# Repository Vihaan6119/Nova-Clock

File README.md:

# Nova Clock

Nova Clock is a desktop alarm clock which uses a Seeed Studio XIAO ESP32-C3. It has a 2.25-inch TFT display, four mechanical keyboard switches, a piezo buzzer and all of these will be on a custom PCB with an enclosure/case where all of these will sit in. The PCB, enclosure, and firmware were all designed as part of the same project so the electronics and the case fit together as one system.

## Why I made it

I wanted to build a project that was more than just a basic clock. I wanted to learn how a real hardware product is build, from designing the PCB and enclosure to writing the firmware and planning how the final device would actually be used.
I also wanted the clock to be something I could keep improving later, especially the display styles, alarms, sounds, and the way it can be used from different device.

## Project

The final design uses a custom PCB with the XIAO ESP32-C3 as the main controller for the clock. The four switches are used for local controls like if the alarm is ringing, then the we can use the switches to turn the alarm off. The TFT display is used for the clock and other information. The buzzer make the sound for the alarms and other things which we like to add.

The enclosure was designed around the PCB so the board can be mounted securely. There is a cutout on the back of the enclosure so that we can easily connect a power/data cable. The display taped onto the lid to make it easier to keep it there without making the build more complex.

## How I planned the firmware

The firmware is included in the repository as a prototype for the hardware design. The main idea is:

- show a short Nova Clock startup animation
- play a startup beep
- display the current time
- use the buttons for local clock and alarm controls
- store alarm settings on the ESP32-C3
- connect the clock to Wi-Fi
- provide a local web interface for changing alarm and display settings
- support different display styles and alarm sound patterns (if the buzzer supports it)

The current firmware is just the PROTOTYPE and will be way different from the current version as after i get all the parts for this build, i will configure them and then properly test and see how eveything is working.

## The enclosure talk

I have started designing the case in openSAD as i thought that this will be the easiest from all the other softwares out there, and it proved me wrong. As i was making the enclosure, it was getting harder to get the precise geomatrical measurements into it, and i also could not check if the PCB all the components would fit in it. 

Then I switched to tinkercad. there i imported PCB, and made the base and the lid. But here too, i did not understand how to make the holes/cutouts in the solids/shapes. 

So then again i switched to Onshape (here i finished making it). I first imported the prototype case i build in tinker cad and tried to build on it. But failed. Then i watched a bunch of tutorials from which, i learn how onshape work. The i started making the PCB enclosure/case. Then after that was done, i imported the PCB .step file. to see if it would fit, and it didn't fit. 

Then I had assembled the full thing. i mean, got all the 3 thing and assembled it showing how it will be looking after i have all the components with me.

## Important thing about viewing the the full assemble .step file

Unfortunaltly, you have to do a little more work in order to see the full assemble 3D model. (You will also come across an error when you upload the .step file of the PCB and the full assembly file. This is due to the 3d model of the ESP32. There is nothing to worry. It is just the issue with the 3D model. I couldn't find a solution to it. )

I have used Onshape in the instruction.

* **uploading:** Import the file **Nova_Clock_Full_Assembly_V4.step** from the folder **CAD** (of my repo).
* It will take aorund 1-2 mins for it to import and load all the file into it.
* **Selecting the file form the menu:** After the import has finished, there will be load and loads of file. From there you have to open 1 file named **Nova_Clock_Full_Assembly**.

## wiring table for display soldering

| PCB Hole | Signal |
| :---: | :--- |
| **1** | GND |
| **2** | +3.3V |
| **3** | SCL |
| **4** | SDA |
| **5** | RST |
| **6** | DC |
| **7** | CS |
| **8** | BL |

The 8 display wires are soldered directly to the display and to the PCB’s J1 holes 
  
## Project images

### Case fit

### PCB

### Schematic / wiring

### Project assembly

.png>)

## Files

The repository has the KiCad project and PCB source files, the CAD source and STEP assembly, the firmware, manufacturing files, and the project images.

- `PCB/` - KiCad project, schematic, PCB layout, and manufacturing files
- `CAD/` - enclosure source files and final STEP assembly
- `Firmware/` - Nova Clock firmware
- `Production/` - production/export files
- `assets/` - screenshots and project images

## Bill of Materials

| Component | Quantity Used | Quantity in Kit | Description | Link |
|---|---:|---:|---|---|
| Seeed Studio XIAO ESP32-C3 | 1 | 1 | Main microcontroller | BLARE Kit |
| MX-style keyboard switch | 4 | 12 | Mechanical switches | BLARE Kit |
| White blank DSA keycap | 4 | 12 | Keycaps for the switches | BLARE Kit |
| 1N4148 through-hole diode | 0 | 12 | Switch matrix diodes | BLARE Kit|
| 2.25-inch TFT display | 1 | 1 | Main clock display | BLARE Kit |
| 3.3 V piezo buzzer | 1 | 1 | Startup and alarm sound | BLARE Kit |
| 2.54 mm 8-pin male header | 1 | 1 | Display connector (only for testing, the final version will have soldered ends) | BLARE Kit |
| 20 cm female-female jumper wire | 8 | 8 | Display wiring (only for testing, the final version will have soldered ends) | BLARE Kit |
| M3x5x4 heat-set insert | 6-8 | 8 | Case, PCB, and display mounting | BLARE Kit |
| M3x8 screw | 2 | 4 | PCB | BLARE Kit |
| M3x16 screw | 4 | 4 | Main enclosure screws | BLARE Kit |
| Custom 2-layer PCB | 1 | 1 | PCB designed in KiCad | [Project PCB](PCB/)  from JLCPCB. Price: $11.1-13.1|
| 3D-printed enclosure | 1 | 1 | Custom Nova Clock case | [Project CAD](CAD/) from printing Legion|

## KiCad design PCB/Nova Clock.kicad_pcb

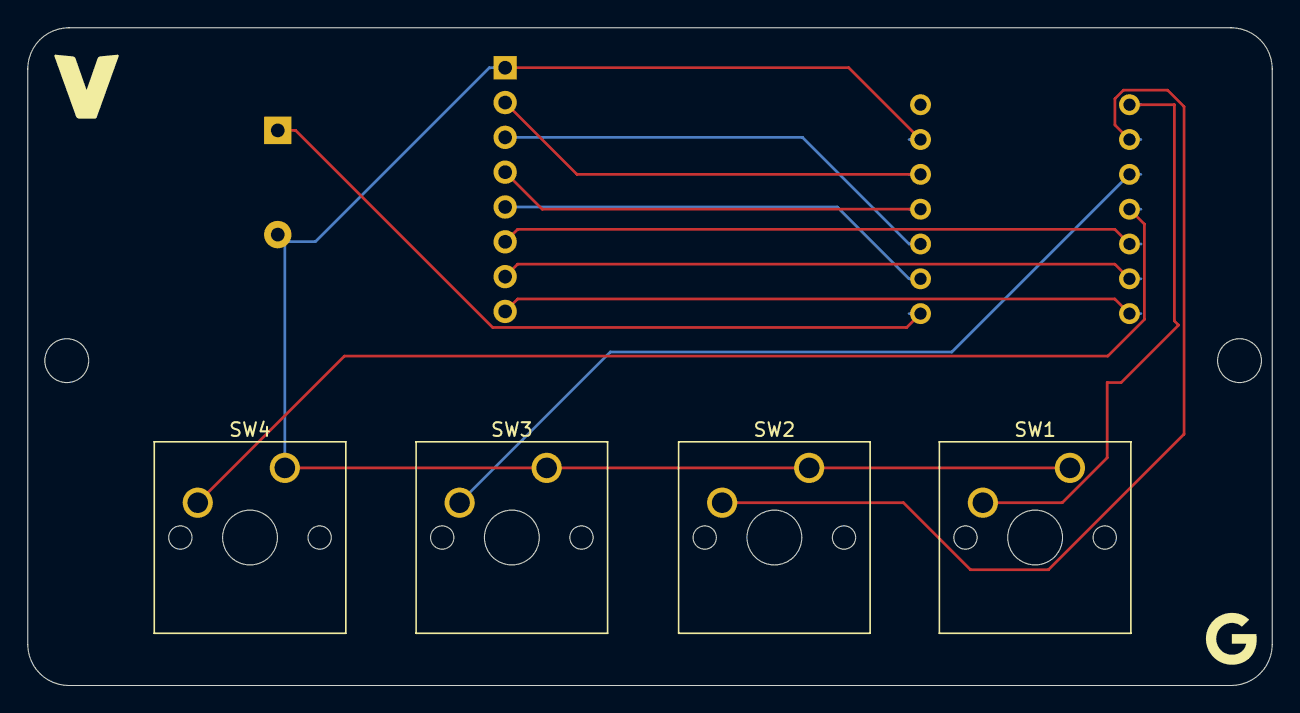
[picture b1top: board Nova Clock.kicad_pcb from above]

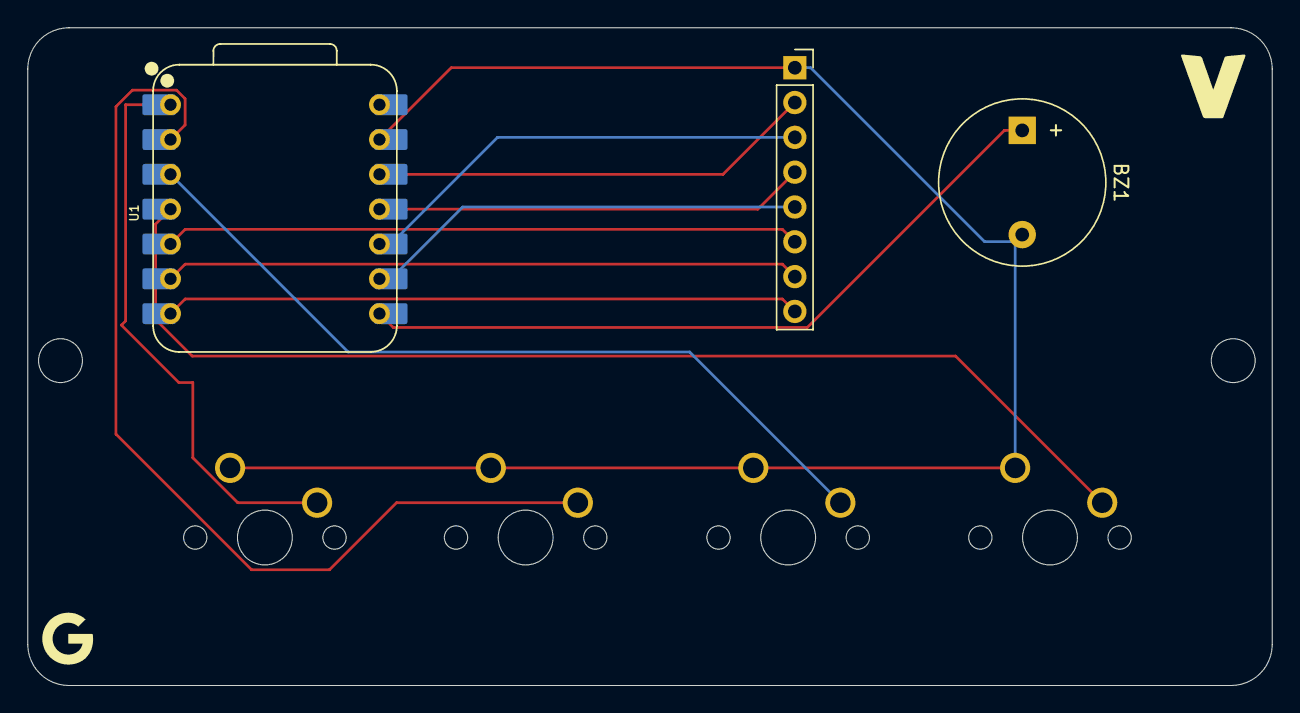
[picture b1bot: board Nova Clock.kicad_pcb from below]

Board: 2 copper layers, 90.8 x 48.0 mm, 9 parts (3 on the bottom side), 13 nets.

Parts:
BZ1: Buzzer; Buzzer_12x9.5RM7.6
H2, H3: MountingHole; MountingHole_3.2mm_M3
J1: Conn_01x08_Pin; PinSocket_1x08_P2.54mm_Vertical
SW1, SW2, SW3, SW4: SW_Push; SW_Cherry_MX_1.00u_PCB
U1: XIAO-ESP32-C3-SMD; XIAO-ESP32-C3-DIP

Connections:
+3.3V: J1.2, U1.12 (3V3_OUT)
/BL: J1.8, U1.7 (D6)
/CS: J1.7, U1.6 (D5)
/DC: J1.6, U1.5 (D4)
/RST: J1.5, U1.9 (D8)
/SCL: J1.3, U1.10 (D9/BOOT)
/SDA: J1.4, U1.11 (D10)
GND: BZ1.2 (-), J1.1, SW1.1, SW2.1, SW3.1, SW4.1, U1.13 (GND)
unnamed: BZ1.1 (+), U1.8 (D7)
unnamed: SW1.2, U1.1 (D0)
unnamed: SW2.2, U1.2 (D1)
unnamed: SW3.2, U1.3 (D2)
unnamed: SW4.2, U1.4 (D3)
